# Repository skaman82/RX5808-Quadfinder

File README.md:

# RX5808-Quadfinder
Modified RX5808 Pro firmware for my Quadfinder project

Changes to the original Version: <br>
• UI overhaul<br>
• 1S voltage monitoring, low-voltage alarm, battery icon in the search UI<br>
• RSSI value in search mode<br>
• RSSI buzzer & LED beacon (configurable in search menu)<br><br>

# Different PCB power options<br>
1s lipo > 5V stepup U3V12F5<br>
2-3s lipo > 5V step-up/down S9V11F5 plus voltage divider R7(18k)+R8(4.7k) > !!!not yet usable, but soon!!!<br><br>

# Materials<br>
Arduino Mini<br>
1.3" OLED I2C Display<br>
3x 6x6x8mm tact buttons<br>
RX5808 SPI Module: <a href="https://de.aliexpress.com/item/1-ST-CK-RX5808-5-8G-SPI-Open-Source-Diversity-Empf-nger-FPV-AV-RX-modul/32852232709.html?spm=a2g0s.9042311.0.0.27424c4d7NSdLk">Link ></a><br>
5V stepup U3V12F5<br>
3.5mm AV socket: <a href="https://de.aliexpress.com/item/50pcs-PJ-320D-3-5mm-4Pin-Audio-Plug-jack-3-5-3-1-Headset-Headphone-Connector/32828520598.html?spm=a2g0s.9042311.0.0.27424c4dz3Jizb">Link ></a><br>
JST-SH 6pin socket<br> 
5v active buzzer SMD: <a href="https://de.aliexpress.com/item/3V-5V-ultra-small-SMD-active-patch-buzzer-9-5mm-9-5mm-5mm-square/1706981111.html?spm=a2g0s.9042311.0.0.27424c4ddocSic">Link ></a><br>
1s lipo: <a href="https://de.aliexpress.com/item/1-st-cke-3-7-v-500-mah-Lithium-Polymer-Batterie-3-7-v-Volt-503035/32950407438.html?spm=a2g0s.9042311.0.0.27424c4d7NSdLk">Link ></a><br>
2x 1206 LEDs (D1, D2)<br>
2x 330 0603 Resistor(R5, R6)<br>
3x 1k 0603 Resistor (R1, R2, R3)<br>
100k 0603 Resistor (R4)<br>
100nF 0603 cap (C1)<br>
10uF 1206 tantalum cap (c2) - optional, bridge otherwise.<br>
Mini slide switch: <a href="https://de.aliexpress.com/item/20-st-cke-MSS22D18-Mini-DIP-Schiebeschalter-1P2T-3Pin-f-r-DIY-Elektronische-Zubeh-r-Mikroschalter/32859694454.html?spm=a2g0s.9042311.0.0.27424c4ddocSic">Link ></a><br>
500mAh Lipo charger: <a href="https://www.banggood.com/Lantian-1S-3_7V-4_2V-0_4A-Android-Micro-USB-Lipo-Battery-Charger-Board-Module-for-FPV-RC-Drone-p-1347517.html?p=03160313547712015036">Link ></a><br>
4x M3 brass inserts and 4x M3 screws<br>
11mm SMA PCB socket

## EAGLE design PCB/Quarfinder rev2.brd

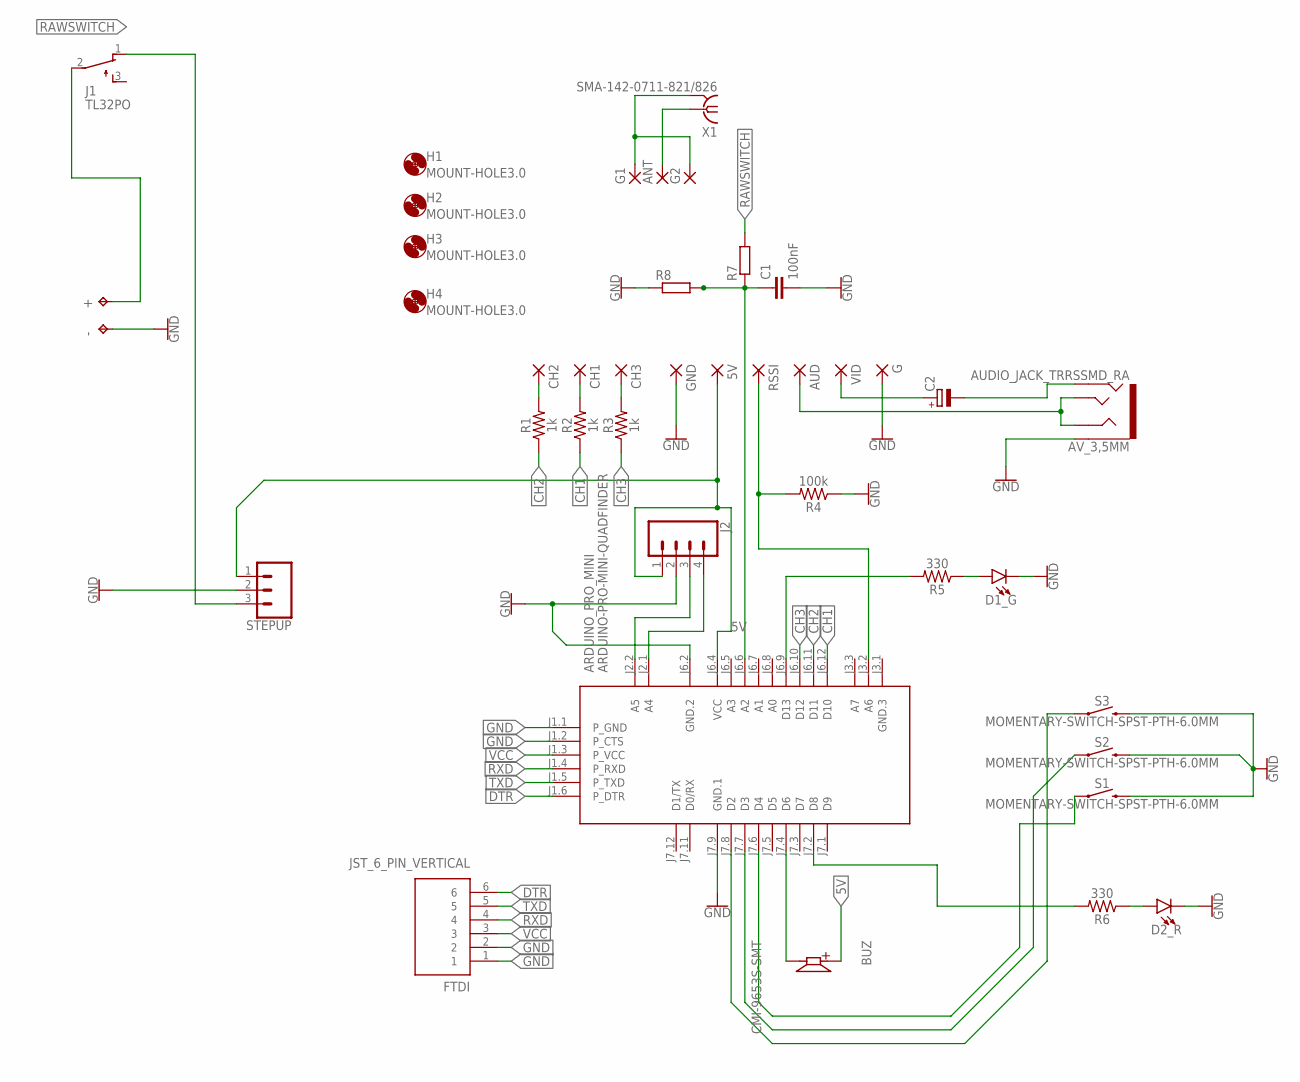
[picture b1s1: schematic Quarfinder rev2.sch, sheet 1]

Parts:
5V: SMD2; SMD1,27-2,54
+: TPTP20R; TP20R
-: TPTP20R; TP20R
ANT: SMD2; SMD1,27-2,54
ARDUINO_PRO_MINI: ARDUINO-PRO-MINI-QUADFINDER; ARDUINO-PRO-MINI
AUD: SMD2; SMD1,27-2,54
AV_3,5MM: AUDIO_JACK_TRRSSMD_RA; AUDIO_JACK_3.5MM_TRRS_SMD_RA
BUZ: CMI-9653S-SMT; CUI_CMI-9653S-SMT
C1: 100nF; 0603
C2: CPOL-EUD/7343-31R; D/7343-31R
CH1, CH2, CH3: SMD2; SMD1,27-2,54
D1_G, D2_R: LED1206; LED-1206
FTDI: JST_6_PIN_VERTICAL; JST-6-SMD-VERT-1.0MM
G, G1, G2: SMD2; SMD1,27-2,54
GND: SMD2; SMD1,27-2,54
H1, H2, H3, H4: MOUNT-HOLE3.0; 3,0
J1: TL32PO; TL3XPO
J2: CONN_04; 1X04
R1, R2, R3: 1k; 0603
R4: 100k; 0603
R5, R6: 330; 0603
R7, R8: R-EU_R1206; R1206
RSSI: SMD2; SMD1,27-2,54
S1, S2, S3: MOMENTARY-SWITCH-SPST-PTH-6.0MM; TACTILE_SWITCH_PTH_6.0MM
STEPUP: CONN_03; 1X03
VID: SMD2; SMD1,27-2,54
X1: SMA-142-0711-821/826; J502-ND-142-0711-821/826

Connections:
5V: 5V.1, ARDUINO_PRO_MINI.J6.4 (VCC), BUZ.P, J2.1, STEPUP.1
CH1: ARDUINO_PRO_MINI.J6.12 (D10), R2.1
CH2: ARDUINO_PRO_MINI.J6.11 (D11), R1.1
CH3: ARDUINO_PRO_MINI.J6.10 (D12), R3.1
DTR: ARDUINO_PRO_MINI.J1.6 (P_DTR), FTDI.6
GND: -.TP, ARDUINO_PRO_MINI.J1.1 (P_GND), ARDUINO_PRO_MINI.J1.2 (P_CTS), ARDUINO_PRO_MINI.J6.2 (GND.2), ARDUINO_PRO_MINI.J7.9 (GND.1), AV_3,5MM.EARTH, C1.2, D1_G.C, D2_R.C, FTDI.1, FTDI.2, G.1, G1.1, G2.1, GND.1, J2.2, R4.1, R8.1, S1.3 (2), S2.3 (2), S3.3 (2), STEPUP.2, X1.G@1 (2), X1.G@2 (2), X1.G@3 (2), X1.G@4 (2)
unnamed: ANT.1, X1.1
unnamed: C2.+, VID.1
unnamed: CH2.1, R1.2
unnamed: CH1.1, R2.2
unnamed: CH3.1, R3.2
unnamed: ARDUINO_PRO_MINI.J2.1 (A4), J2.4
unnamed: ARDUINO_PRO_MINI.J2.2 (A5), J2.3
unnamed: ARDUINO_PRO_MINI.J3.2 (A6), R4.2, RSSI.1
unnamed: ARDUINO_PRO_MINI.J7.8 (D2), S3.1
unnamed: ARDUINO_PRO_MINI.J7.4 (D6), BUZ.N
unnamed: ARDUINO_PRO_MINI.J7.7 (D3), S2.1
unnamed: ARDUINO_PRO_MINI.J7.6 (D4), S1.1
unnamed: D1_G.A, R5.1
unnamed: ARDUINO_PRO_MINI.J6.9 (D13), R5.2
unnamed: D2_R.A, R6.1
unnamed: AUD.1, AV_3,5MM.RING1, AV_3,5MM.TIP
unnamed: ARDUINO_PRO_MINI.J7.2 (D8), R6.2
unnamed: AV_3,5MM.RING2, C2.-
unnamed: ARDUINO_PRO_MINI.J6.6 (A2), C1.1, R7.1, R8.2
RAWSWITCH: J1.1 (O), R7.2, STEPUP.3
RXD: ARDUINO_PRO_MINI.J1.4 (P_RXD), FTDI.4
TXD: ARDUINO_PRO_MINI.J1.5 (P_TXD), FTDI.5
VCC: ARDUINO_PRO_MINI.J1.3 (P_VCC), FTDI.3
VIN: +.TP, J1.2

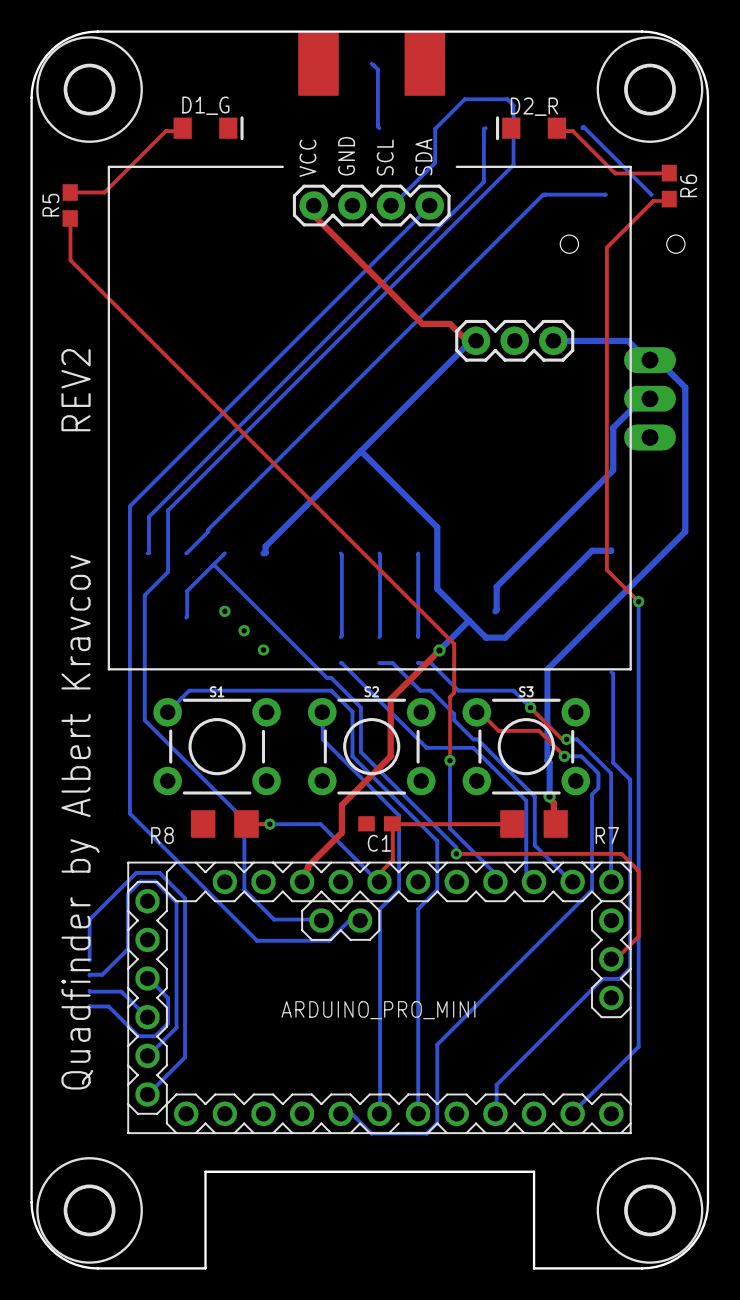
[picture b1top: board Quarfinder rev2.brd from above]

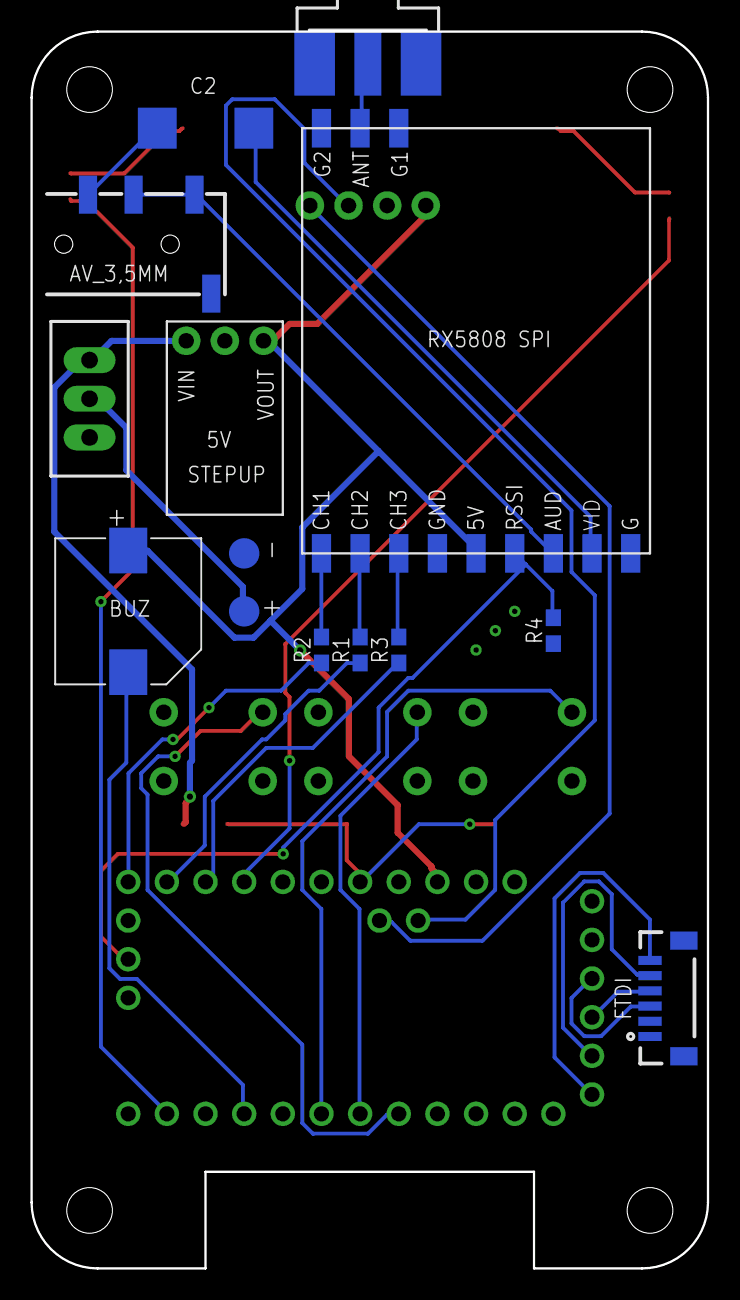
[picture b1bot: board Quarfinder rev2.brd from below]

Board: 2 copper layers, 44.4 x 81.3 mm, 41 parts (24 on the bottom side), 30 nets.

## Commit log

2019-01-04 upload current work state
2019-01-04 ui update
2019-01-04 UI: better low voltage warning
2019-01-04 improved buzzer alarm
2019-01-04 battery animation
2019-01-04 new search menu icon
2019-01-05 fixed side effects between auto search and beacon
2019-01-05 fixed typo
2019-01-05 another typo ;)
2019-01-05 final pcb
2019-01-05 cleanup
2019-01-21 Initial Case work
2019-01-22 Case v1
2019-01-23 Some more work on the case
2019-01-29 LED and Buzzer bugfix
2019-01-29 Final case
2019-01-29 images

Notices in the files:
parts and their libraries:
diy-modules: Released under the Creative Commons Attribution 4.0 International License: http://creativecommons.org/licenses/by/4.0
SparkFun-Connectors: Licensing: Creative Commons ShareAlike 4.0 International - https://creativecommons.org/licenses/by-sa/4.0
